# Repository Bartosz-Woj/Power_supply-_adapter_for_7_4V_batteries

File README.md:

# Custom Power Supply Adapter for 7.4V batteries

## Project Description

The idea of this project is to create a **simple adapter** that allows using a **9 V (or higher)** DC power source instead of the original **7.4 V Li-ion battery** — specifically for the **Panasonic Lumix G7 camera**, using the **DMW-DCC8 DC coupler**.

This solution provides a regulated **8.55 V / 2 A** output suitable for continuous camera operation without relying on battery power.

This PCB can be used to replace a battery/accumulator in other similar applications.

---

## Technical Specifications

| Parameter          | Description                           |
| ------------------ | ------------------------------------- |
| **Input Voltage**  | 9 V – 20 V DC                         |
| **Output Voltage** | 8.55 V DC                              |
| **Output Current** | 2 A (max)                             |
| **Protection**     | Overcurrent fuse and ESD protection   |
| **Connector**      | Screw terminal connector (raster 5mm) |

---

## Battery Voltage Background

A typical **2S Li-ion battery pack** (used in cameras like the Lumix G7) has a **nominal voltage of 7.4 V**, but it varies depending on the charge level:

| Battery State    | Approx. Voltage |
| ---------------- | --------------- |
| Fully Discharged | 6.0 V           |
| Nominal          | 7.4 V           |
| Fully Charged    | 8.4 V           |

Initially, a resistor **R6** (8.66 kOhm) was selected to provide an output of **7.4V**, targeting a nominal 7.4 V equivalent output.

However, this voltage caused the camera to display the error:

> _"This battery cannot be used."_

and automatically power off after a few seconds.

After further research and forum discussions [[thread 1](https://www.dpreview.com/forums/post/59409259)] [[thread 2](https://dprevived.com/t/panasonic-s-series-standby-power-updated-with-s5m2/4551/)], it was discovered that the **Lumix G7** expects a slightly higher voltage (over 8.4V) to correctly identify the source as an **external power supply** rather than a battery. The manufacturer's documentation did not specify the allowable maximum supply voltage. Therefore, it was decided to set the threshold only slightly above the maximum cell voltage.

Currenct consumption was checked with usage of laboratory power supply.The average current consumption is 0.3A, but momentary peaks, especially during startup and photo taking, reach above 1A.

---

## Adjustment of output voltage

The output voltage is determined by a resistor divider network:

$$
V_{\text{out}} = V_{\text{ref}}\left(1 + \dfrac{R_5}{R_6}\right)
$$

For used step down converter (TPS54202):
$$ V\_{ref} = 0.596\,V $$

Example values:
| R5 | R6 | Output voltage |
| --- | ---- | -------------- |
| 100k | 8.66k | 7.4V |
| 100k | 7.5k | 8.55V |

** Note:** The TVS diode's operating voltage sets the maximum output voltage at 8.55V.
---

## 📸 Photos

- **📷 Project Overview:**  

- **🔌 Circuit Board / PCB:**  

---

## Author

- **Project by:** Bartosz-Woj (Bartosz Wojciechowski)
- **Date:** 03.11.2025

---

## Disclaimer

> ⚠️ **Important Notice**

This project is a **custom-made modification** and **not approved by Panasonic** or any official manufacturer.  
Using this power adapter **may void your warranty** and **can potentially damage your device** if built or used incorrectly.

The author of this project **does not take responsibility** for any **damage, data loss, or warranty issues** resulting from the use of this adapter.

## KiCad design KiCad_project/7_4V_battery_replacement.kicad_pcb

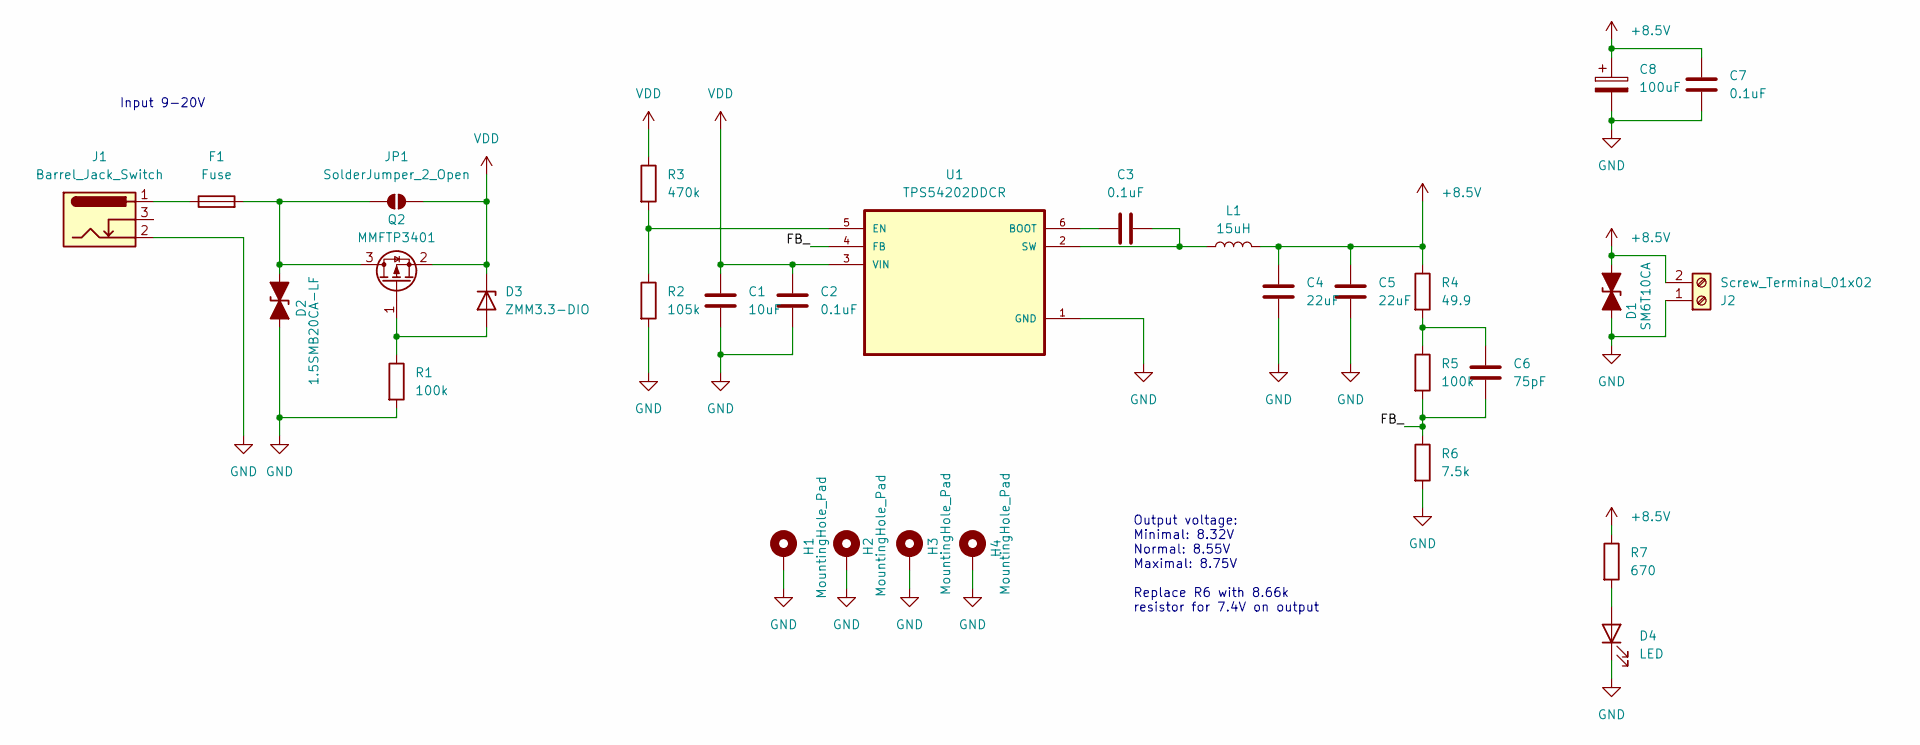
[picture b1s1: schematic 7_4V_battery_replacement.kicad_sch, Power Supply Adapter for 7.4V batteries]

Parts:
C1: 10uF; C_1206_3216Metric_Pad1.33x1.80mm_HandSolder
C2, C3, C7: 0.1uF; C_0603_1608Metric_Pad1.08x0.95mm_HandSolder
C4, C5: 22uF; C_1206_3216Metric_Pad1.33x1.80mm_HandSolder
C6: 75pF; C_0603_1608Metric_Pad1.08x0.95mm_HandSolder
C8: 100uF; CP_Elec_8x10.5
D1: SM6T10CA; D_SMB_Handsoldering
D2: 1.5SMB20CA-LF; D_SMB_Handsoldering
D3: ZMM3.3-DIO; D_MiniMELF
D4: LED; LED_1206_3216Metric_Pad1.42x1.75mm_HandSolder
F1: Fuse; Fuseholder_Littelfuse_Nano2_154x
H1, H2, H3, H4: MountingHole_Pad; MountingHole_3.2mm_M3_DIN965_Pad_TopBottom
J1: Barrel_Jack_Switch; BarrelJack_GCT_DCJ200-10-A_Horizontal
J2: Screw_Terminal_01x02; TerminalBlock_Phoenix_MKDS-1,5-2-5.08_1x02_P5.08mm_Horizont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
JP1: SolderJumper_2_Open; SolderJumper-2_P1.3mm_Open_RoundedPad1.0x1.5mm
L1: 15uH; L_Bourns_SRR1208_12.7x12.7mm
Q2: MMFTP3401; SOT-23
R1, R5: 100k; R_0603_1608Metric_Pad0.98x0.95mm_HandSolder
R2: 105k; R_0603_1608Metric_Pad0.98x0.95mm_HandSolder
R3: 470k; R_0603_1608Metric_Pad0.98x0.95mm_HandSolder
R4: 49.9; R_0603_1608Metric_Pad0.98x0.95mm_HandSolder
R6: 7.5k; R_0603_1608Metric_Pad0.98x0.95mm_HandSolder
R7: 670; R_0603_1608Metric_Pad0.98x0.95mm_HandSolder
U1: TPS54202DDCR; SOT95P280X110-6N

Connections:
+8.5V: C4.1, C5.1, C7.1, C8.1, D1.1 (A1), J2.2, L1.2, R4.1, R7.1
/FB_: C6.2, R5.2, R6.1, U1.4 (FB)
GND: C1.2, C2.2, C4.2, C5.2, C7.2, C8.2, D1.2 (A2), D2.2 (A2), D4.1 (K), H1.1, H2.1, H3.1, H4.1, J1.2, J2.1, R1.2, R2.2, R6.2, U1.1 (GND)
unnamed: C6.1, R4.2, R5.1
unnamed: D2.1 (A1), F1.2, JP1.1 (A), Q2.3 (D)
unnamed: D3.2 (A), Q2.1 (G), R1.1
unnamed: D4.2 (A), R7.2
unnamed: F1.1, J1.1
unnamed: C3.1, U1.6 (BOOT)
unnamed: R2.1, R3.2, U1.5 (EN)
unnamed: C3.2, L1.1, U1.2 (SW)
VDD: C1.1, C2.1, D3.1 (K), JP1.2 (B), Q2.2 (S), R3.1, U1.3 (VIN)

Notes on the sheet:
Input 9-20V
Output voltage: Minimal: 8.32V Normal: 8.55V Maximal: 8.75V Replace R6 with 8.66k resistor for 7.4V on output

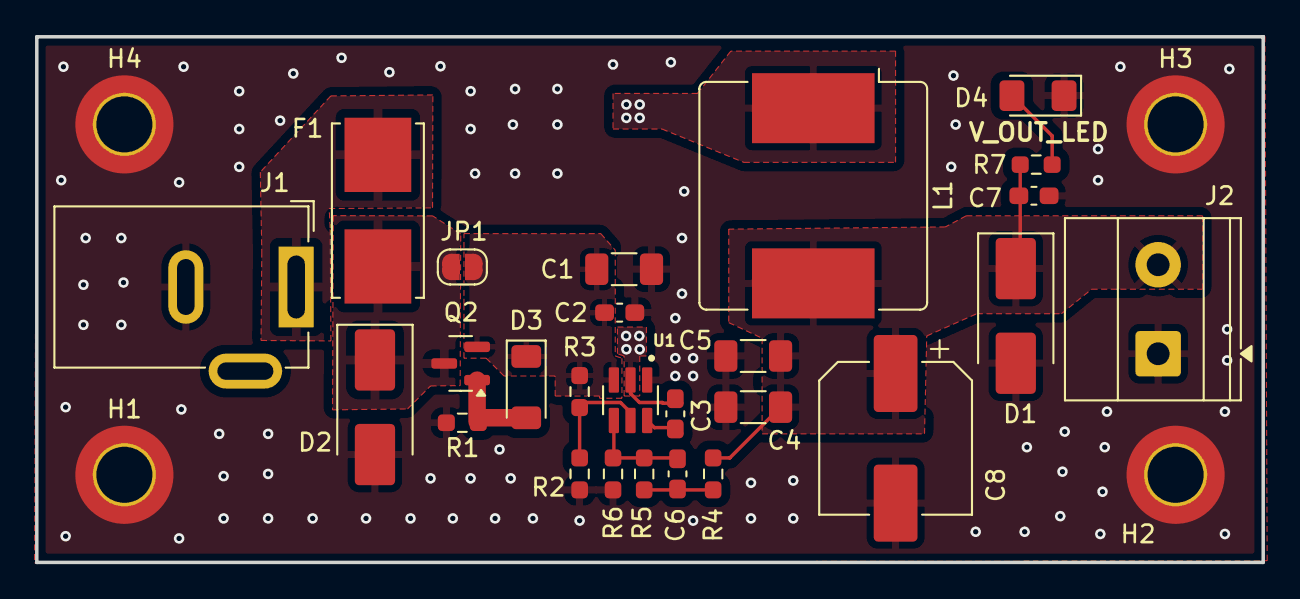
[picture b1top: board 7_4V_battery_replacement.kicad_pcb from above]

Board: 2 copper layers, 70.0 x 30.0 mm, 30 parts (0 on the bottom side), 12 nets.

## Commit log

2025-11-03 initial release
